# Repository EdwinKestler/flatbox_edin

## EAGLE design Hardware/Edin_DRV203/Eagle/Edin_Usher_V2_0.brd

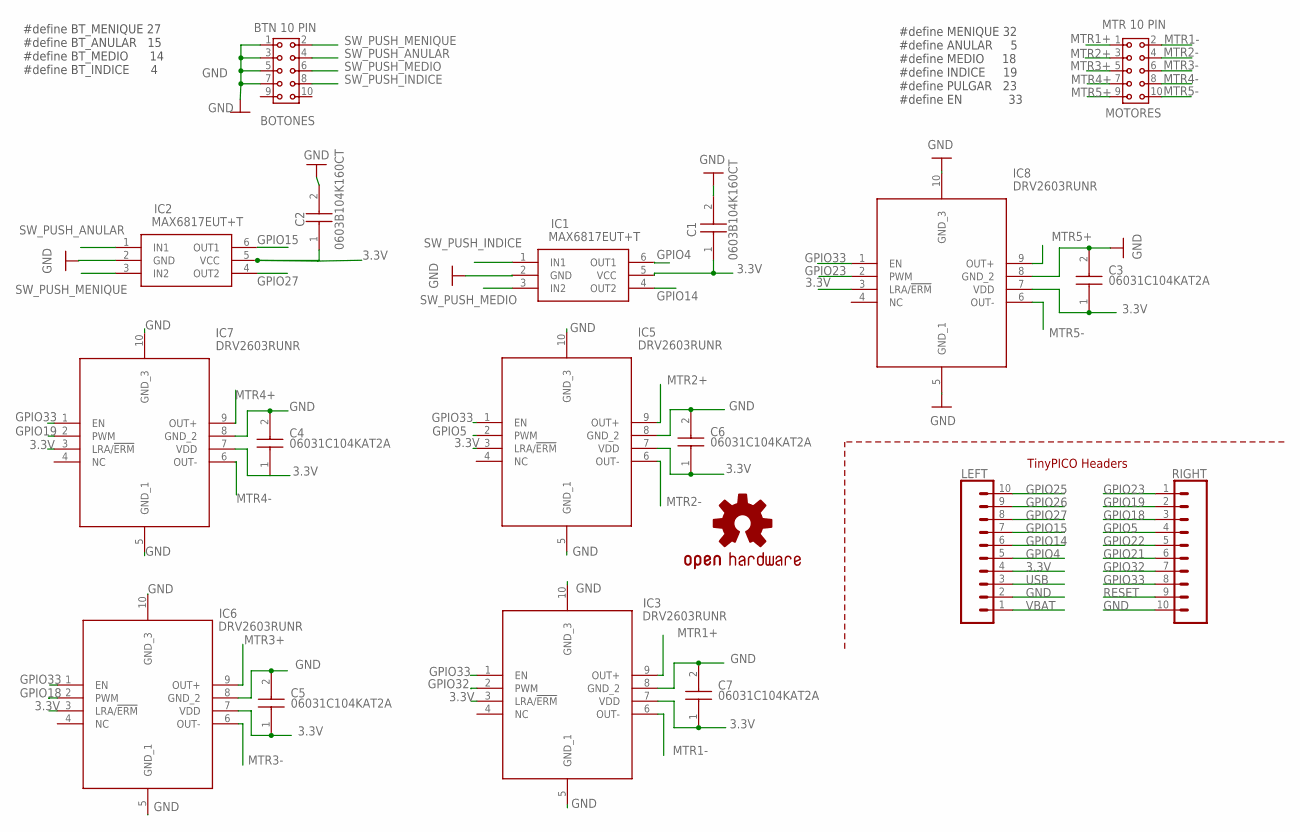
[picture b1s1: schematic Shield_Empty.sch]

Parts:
BOTONES: BTN 10 PIN; 61301021821
C1, C2: 0603B104K160CT; CAPC1608X87N
C3, C4, C5, C6, C7: 06031C104KAT2A; CAPC1608X90N
IC1, IC2: MAX6817EUT+T; SOT95P280X145-6N
IC3, IC5, IC6, IC7, IC8: DRV2603RUNR; QFN50P200X200X80-10N
LEFT: TINYPICO_HEADER_10NO_SILK_PTH_FEMALE; 1X10_NO_SILK
LOGO1: OSHW-LOGOS; OSHW-LOGO-S
MOTORES: MTR 10 PIN; 61301021821
RIGHT: TINYPICO_HEADER_10NO_SILK_PTH_FEMALE; 1X10_NO_SILK

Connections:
3.3V: C1.1, C2.1, C3.1, C4.1, C5.1, C6.1, C7.1, IC1.5 (VCC), IC2.5 (VCC), IC3.3 (LRA/!ERM), IC3.7 (VDD), IC5.3 (LRA/!ERM), IC5.7 (VDD), IC6.3 (LRA/!ERM), IC6.7 (VDD), IC7.3 (LRA/!ERM), IC7.7 (VDD), IC8.3 (LRA/!ERM), IC8.7 (VDD), LEFT.4
GND: BOTONES.1, BOTONES.3, BOTONES.5, BOTONES.7, C1.2, C2.2, C3.2, C4.2, C5.2, C6.2, C7.2, IC1.2 (GND), IC2.2 (GND), IC3.5 (GND_1), IC3.8 (GND_2), IC3.10 (GND_3), IC5.5 (GND_1), IC5.8 (GND_2), IC5.10 (GND_3), IC6.5 (GND_1), IC6.8 (GND_2), IC6.10 (GND_3), IC7.5 (GND_1), IC7.8 (GND_2), IC7.10 (GND_3), IC8.5 (GND_1), IC8.8 (GND_2), IC8.10 (GND_3), LEFT.2, RIGHT.10
GPIO4: IC1.6 (OUT1), LEFT.5
GPIO5: IC5.2 (PWM), RIGHT.4
GPIO14: IC1.4 (OUT2), LEFT.6
GPIO15: IC2.6 (OUT1), LEFT.7
GPIO18: IC6.2 (PWM), RIGHT.3
GPIO19: IC7.2 (PWM), RIGHT.2
GPIO21: RIGHT.6
GPIO22: RIGHT.5
GPIO23: IC8.2 (PWM), RIGHT.1
GPIO25: LEFT.10
GPIO26: LEFT.9
GPIO27: IC2.4 (OUT2), LEFT.8
GPIO32: IC3.2 (PWM), RIGHT.7
GPIO33: IC3.1 (EN), IC5.1 (EN), IC6.1 (EN), IC7.1 (EN), IC8.1 (EN), RIGHT.8
MTR1+: IC3.9 (OUT+), MOTORES.1
MTR1-: IC3.6 (OUT-), MOTORES.2
MTR2+: IC5.9 (OUT+), MOTORES.3
MTR2-: IC5.6 (OUT-), MOTORES.4
MTR3+: IC6.9 (OUT+), MOTORES.5
MTR3-: IC6.6 (OUT-), MOTORES.6
MTR4+: IC7.9 (OUT+), MOTORES.7
MTR4-: IC7.6 (OUT-), MOTORES.8
MTR5+: IC8.9 (OUT+), MOTORES.9
MTR5-: IC8.6 (OUT-), MOTORES.10
RESET: RIGHT.9
SW_PUSH_ANULAR: BOTONES.4, IC2.1 (IN1)
SW_PUSH_INDICE: BOTONES.8, IC1.1 (IN1)
SW_PUSH_MEDIO: BOTONES.6, IC1.3 (IN2)
SW_PUSH_MENIQUE: BOTONES.2, IC2.3 (IN2)
USB: LEFT.3
VBAT: LEFT.1

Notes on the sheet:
TinyPICO Headers
#define MENIQUE 32 #define ANULAR 5 #define MEDIO 18 #define INDICE 19 #define PULGAR 23 #define EN 33
#define BT_MENIQUE 27 #define BT_ANULAR 15 #define BT_MEDIO 14 #define BT_INDICE 4

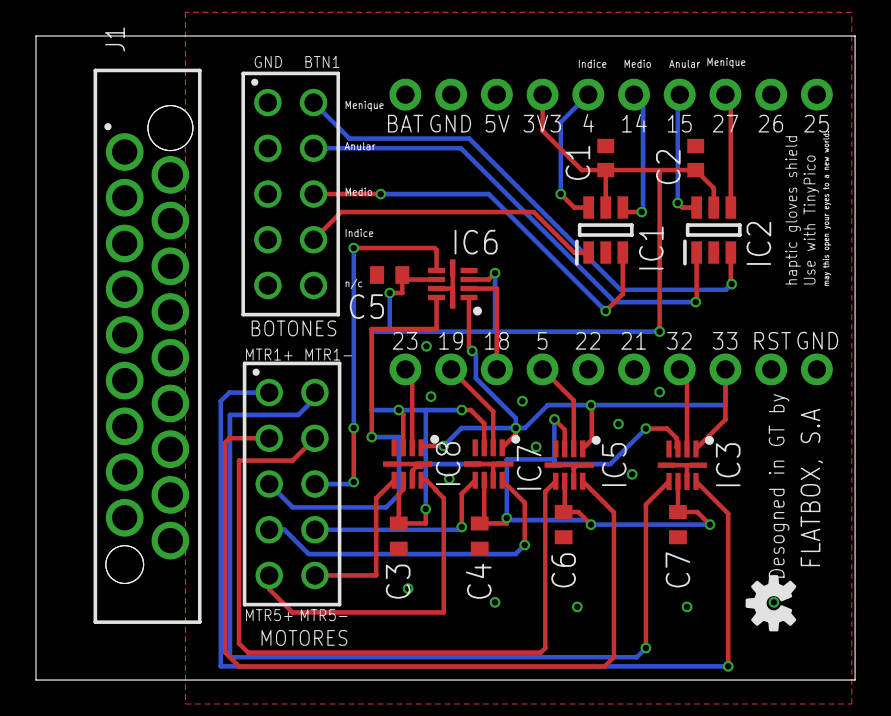
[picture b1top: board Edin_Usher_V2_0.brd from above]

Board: 2 copper layers, 45.5 x 35.8 mm, 21 parts (1 on the bottom side), 26 nets.

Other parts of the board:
J1: 490107671812
LOGO2: OSHW-LOGOS; OSHW-LOGO-S

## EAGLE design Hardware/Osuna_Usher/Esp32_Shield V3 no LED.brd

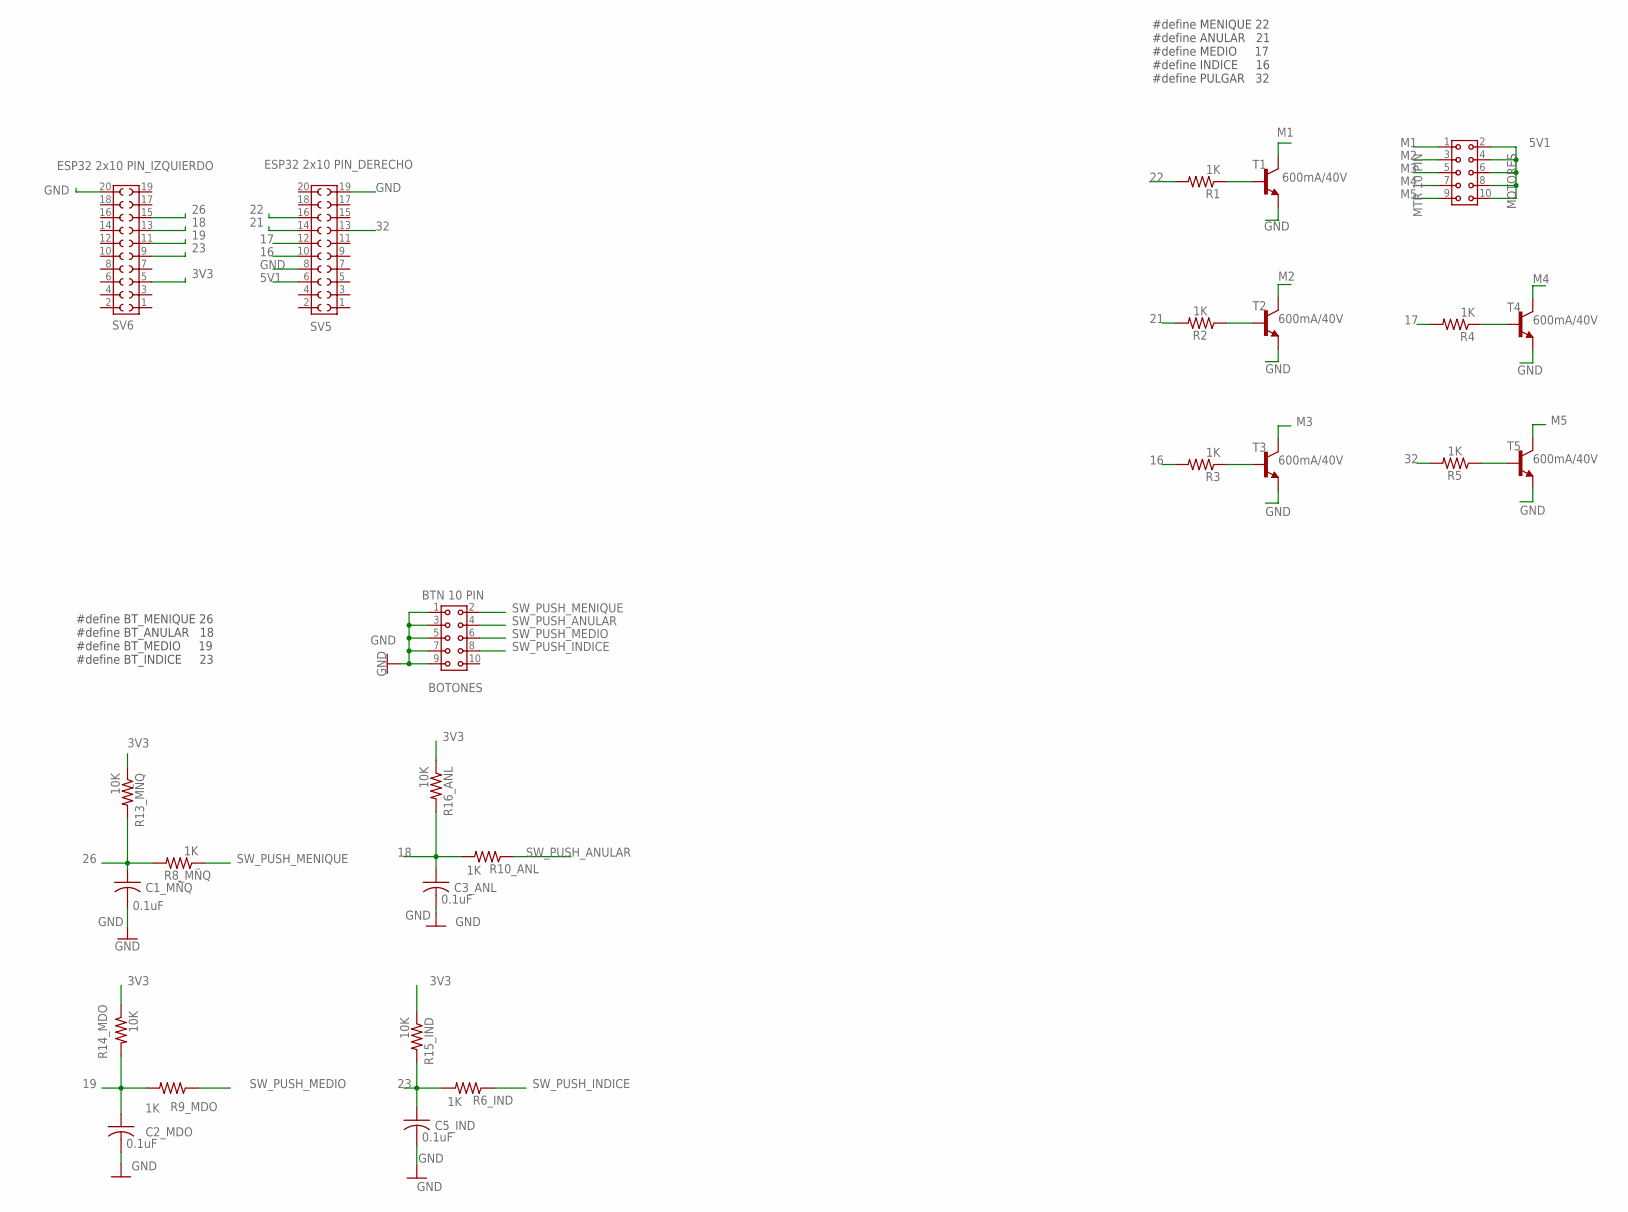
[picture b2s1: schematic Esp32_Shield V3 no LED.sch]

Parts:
BOTONES: BTN 10 PIN; 61301021821
C1_MÑQ, C2_MDO, C3_ANL, C5_IND: 0.1uF; C0805
MOTORES: MTR 10 PIN; 61301021821
R1, R2, R3, R4, R5, R6_IND, R8_MÑQ, R9_MDO, R10_ANL: 1K; R0805
R13_MÑQ, R14_MDO, R15_IND, R16_ANL: 10K; R0805
SV5: ESP32 2x10 PIN_DERECHO; 61302021821
SV6: ESP32 2x10 PIN_IZQUIERDO; 61302021821
T1, T2, T3, T4, T5: 600mA/40V; SOT23-3

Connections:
3V3: R13_MÑQ.1, R14_MDO.1, R15_IND.1, R16_ANL.1, SV6.5
5V1: MOTORES.2, MOTORES.4, MOTORES.6, MOTORES.8, MOTORES.10, SV5.6
16: R3.2, SV5.10
17: R4.2, SV5.12
18: C3_ANL.1, R10_ANL.2, R16_ANL.2, SV6.13
19: C2_MDO.1, R9_MDO.2, R14_MDO.2, SV6.11
21: R2.2, SV5.14
22: R1.2, SV5.16
23: C5_IND.1, R6_IND.2, R15_IND.2, SV6.9
26: C1_MÑQ.1, R8_MÑQ.2, R13_MÑQ.2, SV6.15
32: R5.2, SV5.13
GND: BOTONES.1, BOTONES.3, BOTONES.5, BOTONES.7, BOTONES.9, C1_MÑQ.2, C2_MDO.2, C3_ANL.2, C5_IND.2, SV5.8, SV5.19, SV6.20, T1.2 (E), T2.2 (E), T3.2 (E), T4.2 (E), T5.2 (E)
M1: MOTORES.1, T1.3 (C)
M2: MOTORES.3, T2.3 (C)
M3: MOTORES.5, T3.3 (C)
M4: MOTORES.7, T4.3 (C)
M5: MOTORES.9, T5.3 (C)
unnamed: R2.1, T2.1 (B)
unnamed: R1.1, T1.1 (B)
unnamed: R3.1, T3.1 (B)
unnamed: R4.1, T4.1 (B)
unnamed: R5.1, T5.1 (B)
SW_PUSH_ANULAR: BOTONES.4, R10_ANL.1
SW_PUSH_INDICE: BOTONES.8, R6_IND.1
SW_PUSH_MEDIO: BOTONES.6, R9_MDO.1
SW_PUSH_MENIQUE: BOTONES.2, R8_MÑQ.1

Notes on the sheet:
#define MENIQUE 22 #define ANULAR 21 #define MEDIO 17 #define INDICE 16 #define PULGAR 32
#define BT_MENIQUE 26 #define BT_ANULAR 18 #define BT_MEDIO 19 #define BT_INDICE 23

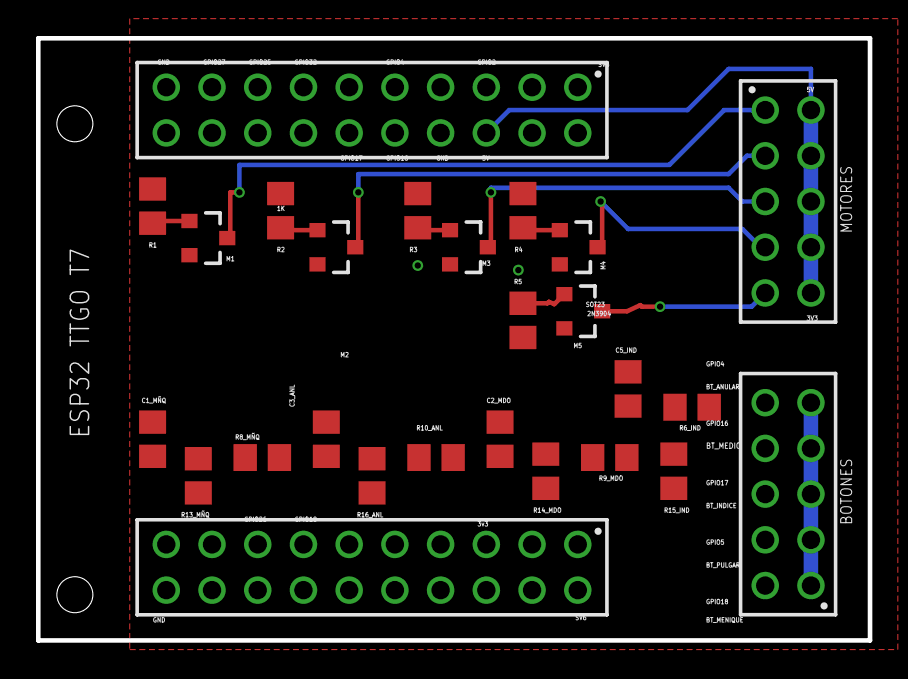
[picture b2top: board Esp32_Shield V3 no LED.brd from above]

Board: 2 copper layers, 46.2 x 33.5 mm, 26 parts (0 on the bottom side), 26 nets.

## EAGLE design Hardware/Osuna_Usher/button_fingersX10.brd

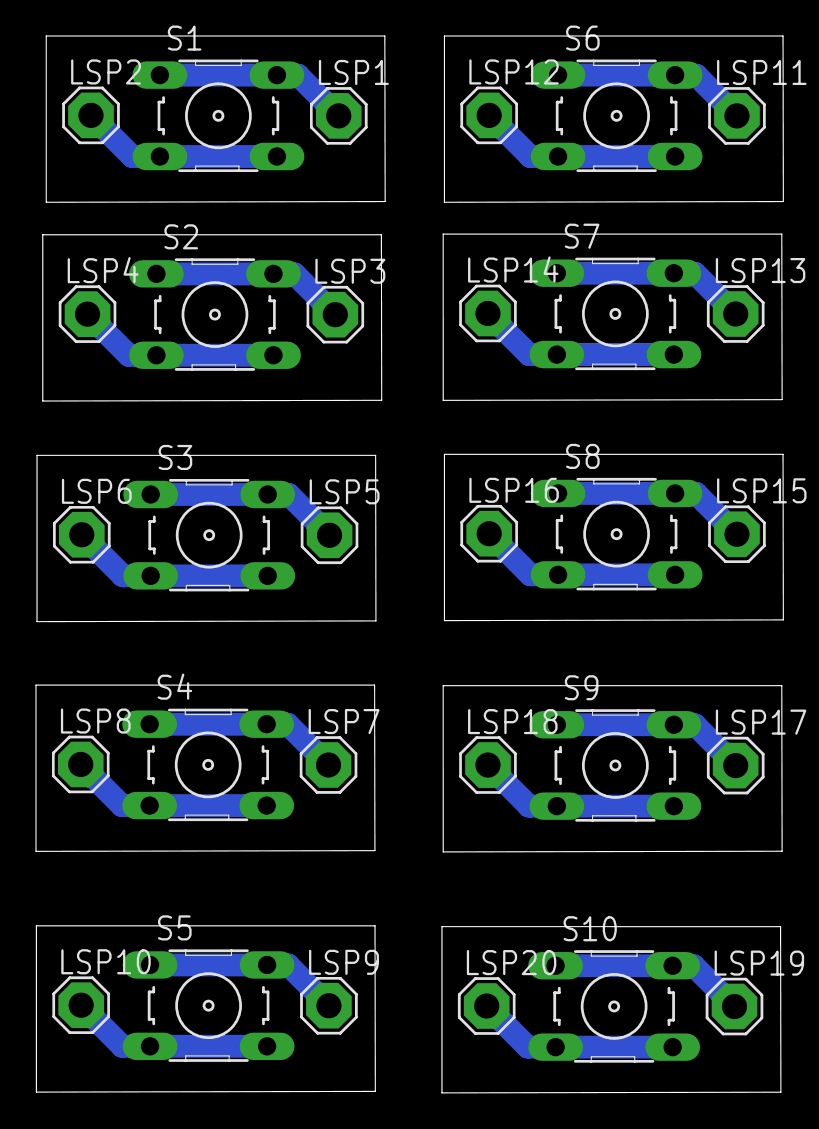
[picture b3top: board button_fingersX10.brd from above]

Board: 2 copper layers, 41.5 x 58.7 mm, 30 parts (0 on the bottom side), 20 nets.

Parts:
LSP1, LSP2, LSP3, LSP4, LSP5, LSP6, LSP7, LSP8, LSP9, LSP10, LSP11, LSP12, LSP13, LSP14, LSP15, LSP16, LSP17, LSP18, LSP19, LSP20: SE14
S1, S2, S3, S4, S5, S6, S7, S8, S9, S10: B3F-10XX

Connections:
unnamed: LSP1.MP, S1.1, S1.2
unnamed: LSP2.MP, S1.3, S1.4
unnamed: LSP3.MP, S2.1, S2.2
unnamed: LSP4.MP, S2.3, S2.4
unnamed: LSP5.MP, S3.1, S3.2
unnamed: LSP6.MP, S3.3, S3.4
unnamed: LSP7.MP, S4.1, S4.2
unnamed: LSP8.MP, S4.3, S4.4
unnamed: LSP9.MP, S5.1, S5.2
unnamed: LSP10.MP, S5.3, S5.4
unnamed: LSP11.MP, S6.1, S6.2
unnamed: LSP12.MP, S6.3, S6.4
unnamed: LSP13.MP, S7.1, S7.2
unnamed: LSP14.MP, S7.3, S7.4
unnamed: LSP15.MP, S8.1, S8.2
unnamed: LSP16.MP, S8.3, S8.4
unnamed: LSP17.MP, S9.1, S9.2
unnamed: LSP18.MP, S9.3, S9.4
unnamed: LSP19.MP, S10.1, S10.2
unnamed: LSP20.MP, S10.3, S10.4

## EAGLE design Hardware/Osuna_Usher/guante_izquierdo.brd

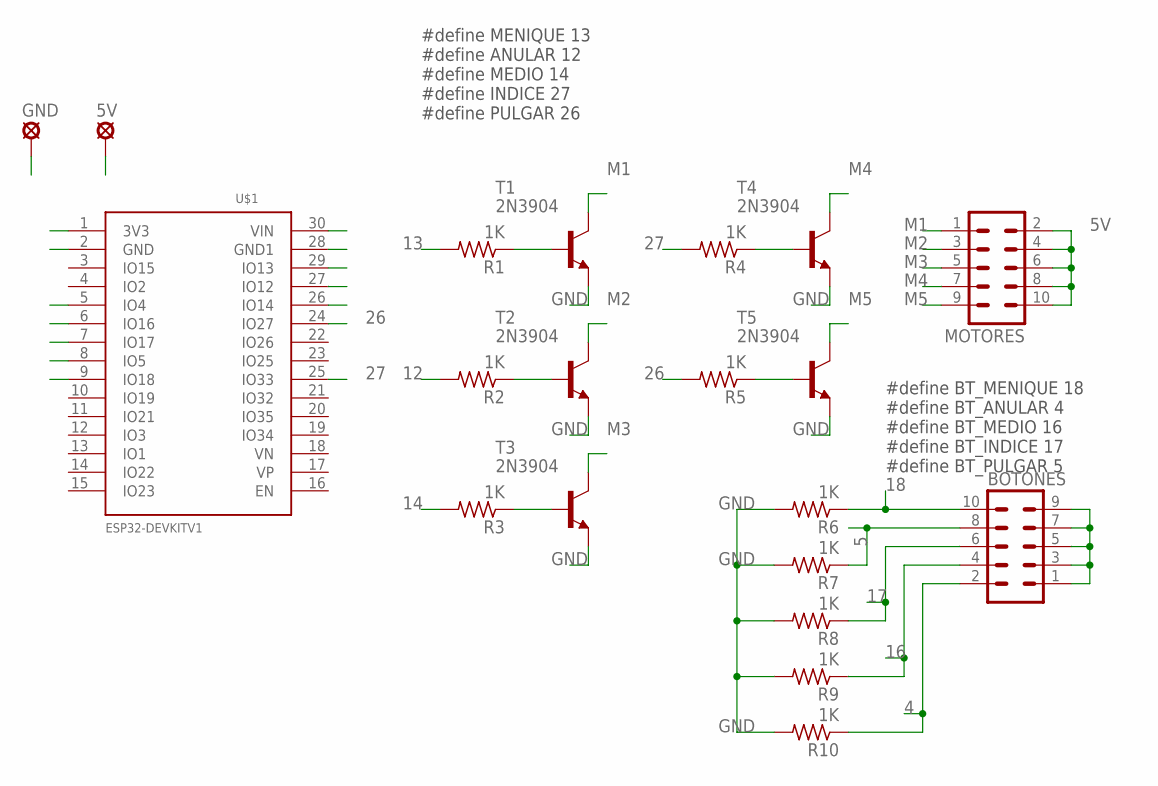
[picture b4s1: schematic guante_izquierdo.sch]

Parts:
5V: MCS10B
BOTONES: MA05-2
GND: MCS10B
MOTORES: MA05-2
R1, R2, R3, R4, R5, R6, R7, R8, R9, R10: 1K; 0207/10
T1, T2, T3, T4, T5: 2N3904; TO92-EBC
U$1: ESP32DEVKITV1; ESP32-DEVKITV1

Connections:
3V3: BOTONES.1, BOTONES.3, BOTONES.5, BOTONES.7, BOTONES.9, U$1.1 (3V3)
4: BOTONES.2, R10.1, U$1.5 (IO4)
5: BOTONES.8, R7.1, U$1.8 (IO5)
5V: 5V.MP, MOTORES.2, MOTORES.4, MOTORES.6, MOTORES.8, MOTORES.10, U$1.30 (VIN)
12: R2.2, U$1.27 (IO12)
13: R1.2, U$1.29 (IO13)
14: R3.2, U$1.26 (IO14)
16: BOTONES.4, R9.1, U$1.6 (IO16)
17: BOTONES.6, R8.1, U$1.7 (IO17)
18: BOTONES.10, R6.1, U$1.9 (IO18)
26: R5.2, U$1.24 (IO27)
27: R4.2, U$1.25 (IO33)
GND: GND.MP, R6.2, R7.2, R8.2, R9.2, R10.2, T1.E, T2.E, T3.E, T4.E, T5.E, U$1.2 (GND), U$1.28 (GND1)
M1: MOTORES.1, T1.C
M2: MOTORES.3, T2.C
M3: MOTORES.5, T3.C
M4: MOTORES.7, T4.C
M5: MOTORES.9, T5.C
unnamed: R2.1, T2.B
unnamed: R1.1, T1.B
unnamed: R3.1, T3.B
unnamed: R4.1, T4.B
unnamed: R5.1, T5.B

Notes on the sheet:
#define MENIQUE 13 #define ANULAR 12 #define MEDIO 14 #define INDICE 27 #define PULGAR 26
#define BT_MENIQUE 18 #define BT_ANULAR 4 #define BT_MEDIO 16 #define BT_INDICE 17 #define BT_PULGAR 5

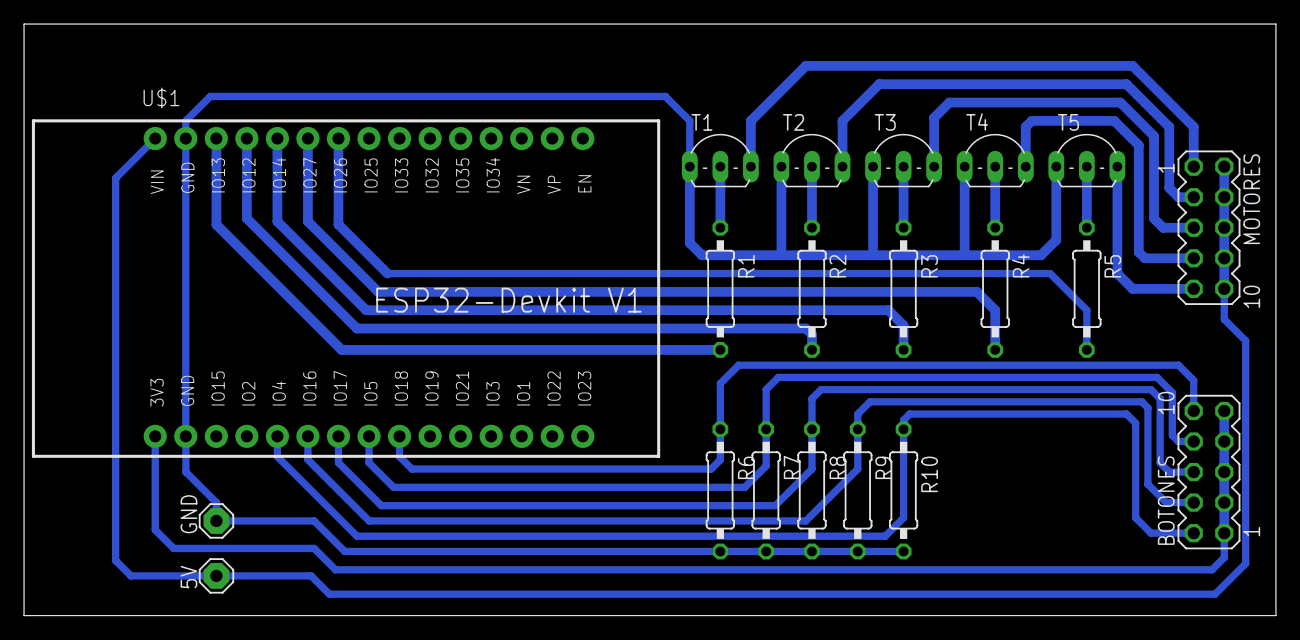
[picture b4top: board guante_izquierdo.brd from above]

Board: 2 copper layers, 104.1 x 49.2 mm, 20 parts (0 on the bottom side), 23 nets.

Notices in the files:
parts and their libraries:
SparkFun-Aesthetics: Licensing: Creative Commons ShareAlike 4.0 International - https://creativecommons.org/licenses/by-sa/4.0
Wurth_Connectors_WR-PHD: Copyright: Würth Elektronik
